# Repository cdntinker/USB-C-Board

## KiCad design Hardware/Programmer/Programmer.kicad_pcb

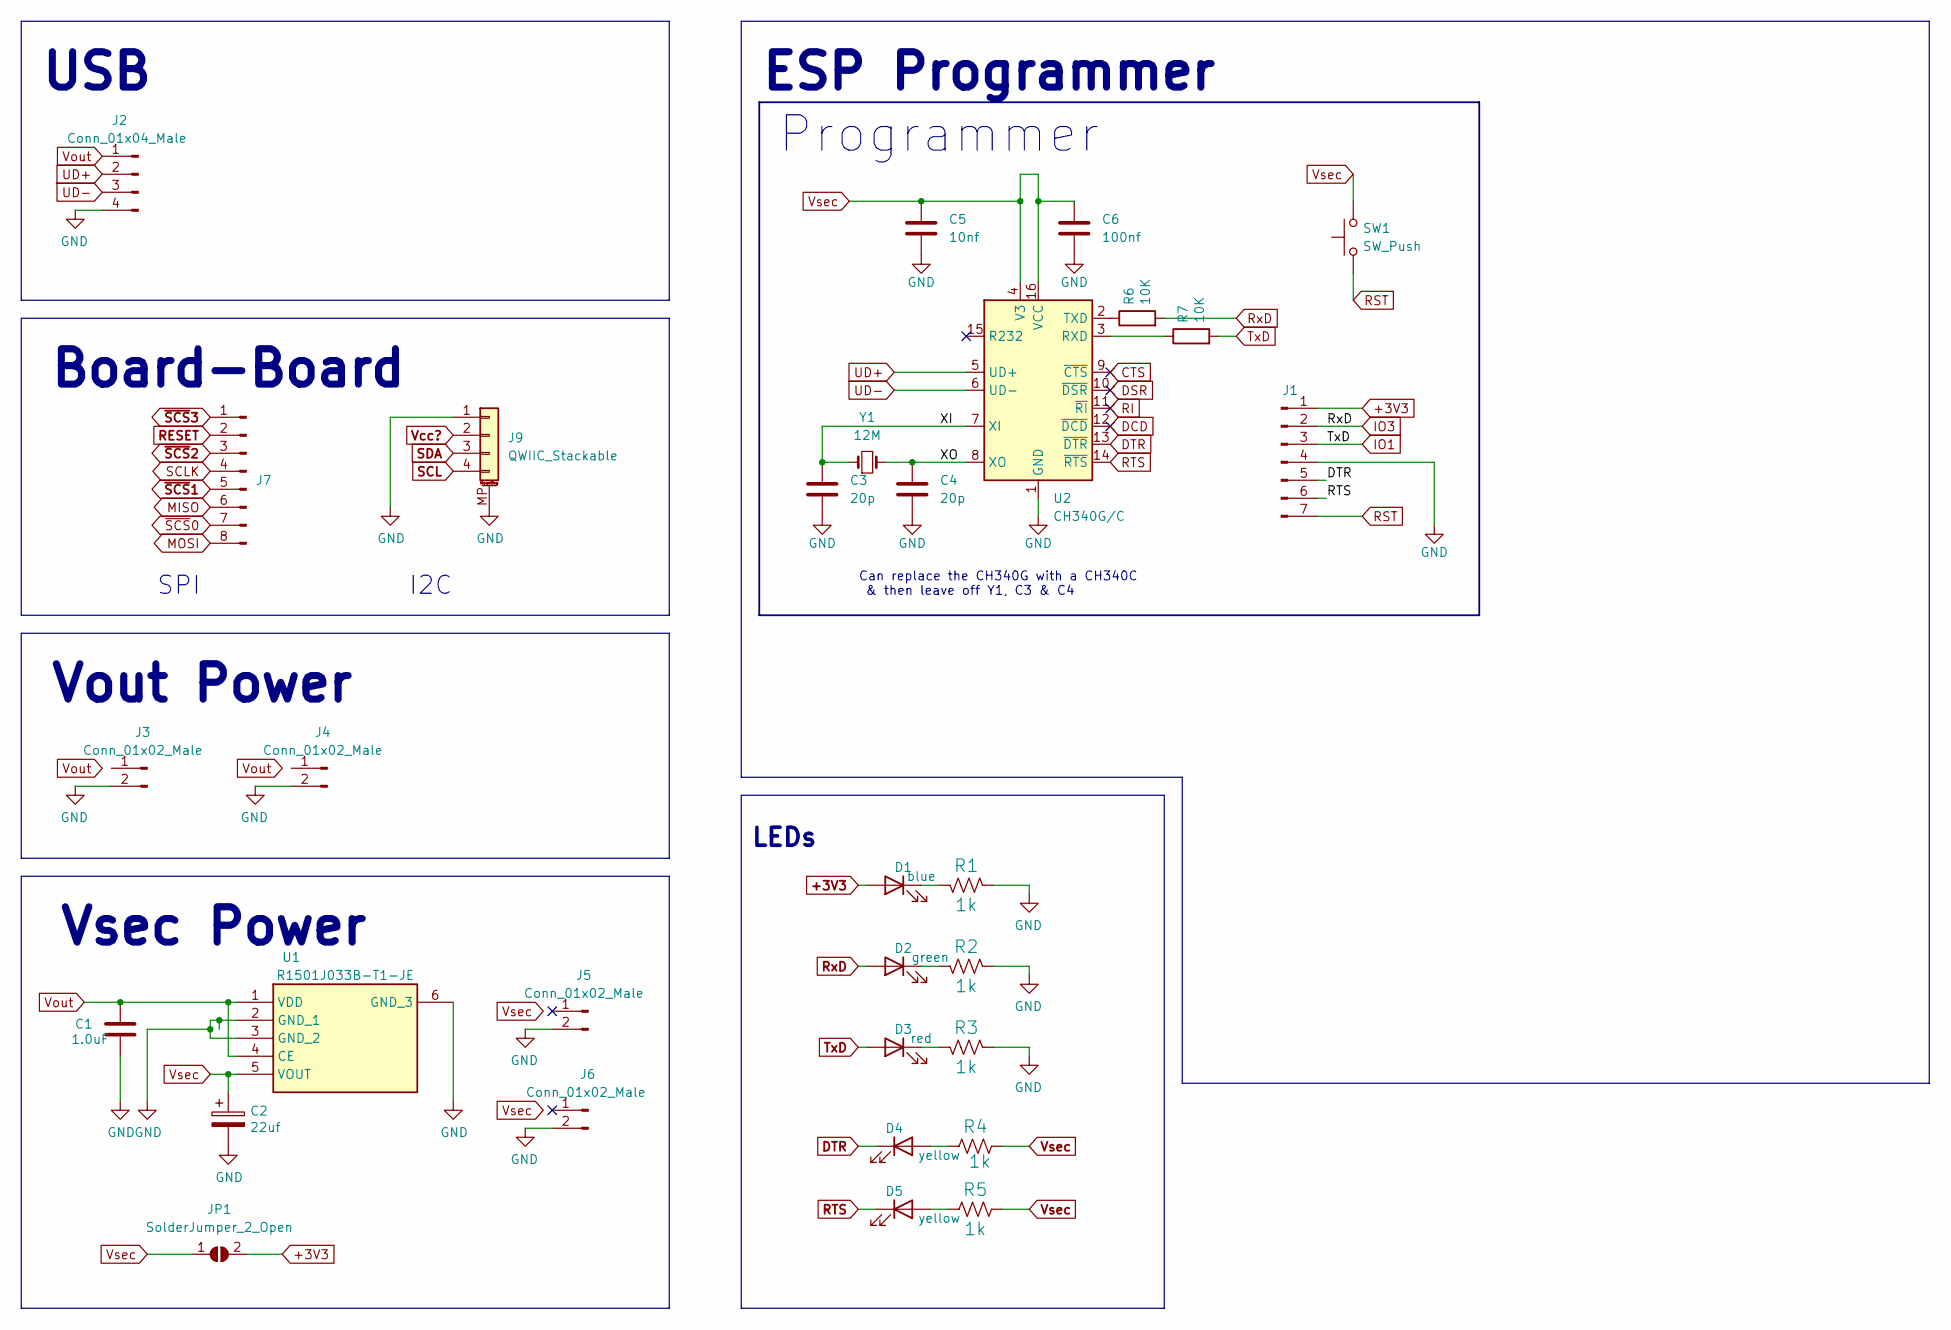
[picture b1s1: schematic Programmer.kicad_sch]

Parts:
C1: 1.0uF; C_0603_1608Metric; LCSC C559769
C2: 22uf; CP_EIA-6032-28-Tantalumm_HandSolder; LCSC C89246
C3, C4: 20p; C_0603_1608Metric_Pad1.08x0.95mm_HandSolder; LCSC C325469
C5: 10nf; C_0603_1608Metric_Pad1.08x0.95mm_HandSolder; LCSC C161232
C6: 100nf; C_0603_1608Metric_Pad1.08x0.95mm_HandSolder; LCSC C235731
D1: blue; LED_0603_1608Metric; LCSC C434420
D2: green; LED_0603_1608Metric; LCSC C434420
D3: red; LED_0603_1608Metric; LCSC C434420
D4: yellow; LED_0603_1608Metric; LCSC C434421
D5: yellow; LED_0603_1608Metric; LCSC C434424
J1: Conn_01x07_Male; Board_Stacker_7
J2: Conn_01x04_Male; Board_Stacker_4
J3, J4, J5, J6: Conn_01x02_Male; Board_Stacker_2
J7: Conn_01x08_Male; PinHeader_2x04_P1.27mm_Vertical; LCSC C2881786 + C2684732
J9: QWIIC_Stackable; QWIIC_Stack_II
JP1: SolderJumper_2_Open; SolderJumper-2_P_Open_Rounded_skinny
R1, R2, R3, R4, R5: 1k; R_0603_1608Metric; LCSC C21190
R6, R7: 10K; R_0603_1608Metric_Pad0.98x0.95mm_HandSolder; LCSC C25804
SW1: SW_Push; SW_Push_TS273014TP; LCSC C2858276
U1: R1501J033B-T1-JE; R1501J033BT1JE; Manufacturer_Part_Number R1501J033B-T1-JE; LCSC C3748149
U2: CH340G/C; SOIC-16_3.9x9.9mm_P1.27mm; LCSC C14267/C84681
Y1: 12M; Crystal_SMD_5032-2Pin_5.0x3.2mm; LCSC C2842275

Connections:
+3V3: D1.2 (A), J1.1, JP1.2 (B)
/XI: C3.1, U2.7 (XI), Y1.1
/XO: C4.1, U2.8 (XO), Y1.2
CTS: U2.9 (~CTS)
DCD: U2.12 (~DCD)
DSR: U2.10 (~DSR)
DTR: D4.1 (K), J1.5, U2.13 (~DTR)
GND: C1.2, C2.2, C3.2, C4.2, C5.2, C6.2, J1.4, J2.4, J3.2, J4.2, J5.2, J6.2, J9.1, J9.MP (MountPin), R1.1, R2.1, R3.1, U1.2 (GND_1), U1.3 (GND_2), U1.6 (GND_3), U2.1 (GND)
IO1: D3.2 (A), J1.3, R7.2
IO3: D2.2 (A), J1.2, R6.2
MISO: J7.6
MOSI: J7.8
unnamed: D1.1 (K), R1.2
unnamed: D2.1 (K), R2.2
unnamed: D3.1 (K), R3.2
unnamed: D4.2 (A), R4.1
unnamed: D5.2 (A), R5.1
unnamed: R6.1, U2.2 (TXD)
unnamed: R7.1, U2.3 (RXD)
RESET: J7.2
RI: U2.11 (~RI)
RST: J1.7, SW1.1
RTS: D5.1 (K), J1.6, U2.14 (~RTS)
SCL: J9.4
SCLK: J7.4
SDA: J9.3
UD+: J2.2, U2.5 (UD+)
UD-: J2.3, U2.6 (UD-)
Vcc?: J9.2
Vout: C1.1, J2.1, U1.1 (VDD), U1.4 (CE)
Vsec: C2.1, C5.1, C6.1, JP1.1 (A), R4.2, R5.2, SW1.2, U1.5 (VOUT), U2.4 (V3), U2.16 (VCC)
~RESET: J7.1
~SCS0: J7.7
~SCS1: J7.5
~SCS2: J7.3

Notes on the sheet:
Vout Power
USB
Programmer
LEDs
Can replace the CH340G with a CH340C & then leave off Y1, C3 & C4
I2C
Board-Board
ESP Programmer
Vsec Power
SPI

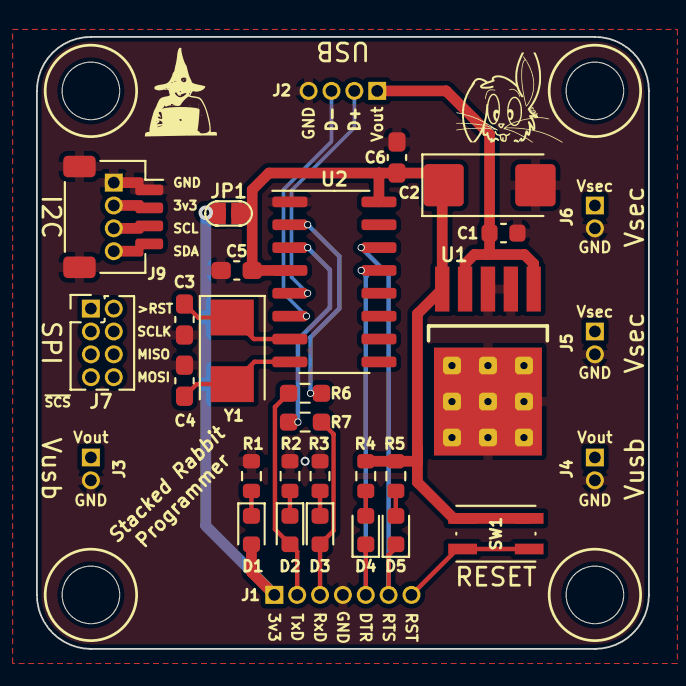
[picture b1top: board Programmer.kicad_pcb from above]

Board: 2 copper layers, 34.0 x 34.0 mm, 31 parts (0 on the bottom side), 20 nets.

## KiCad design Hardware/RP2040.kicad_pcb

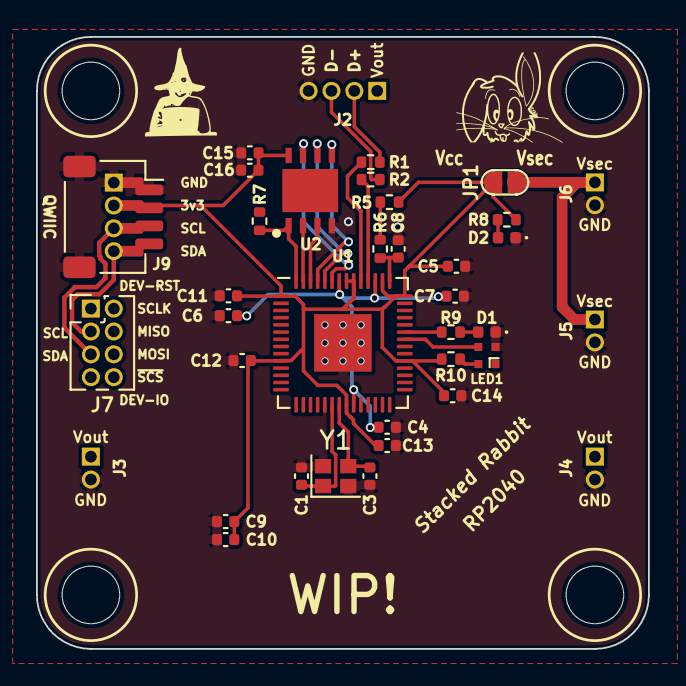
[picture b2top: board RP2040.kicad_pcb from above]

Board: 2 copper layers, 34.0 x 34.0 mm, 37 parts (0 on the bottom side), 25 nets.

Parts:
C1, C3: 20p; C_0402_1005Metric
C4, C5, C8, C15: 2u2; C_0402_1005Metric
C6, C7, C9, C10, C11, C12, C13, C14, C16: 100n; C_0402_1005Metric
D1, D2: LED; LED_0402_1005Metric
J2: Conn_01x04_Male; Board_Stacker_4
J3, J4, J5, J6: Conn_01x02_Male; Board_Stacker_2
J7: Conn_01x08_Male; PinHeader_2x04_P1.27mm_Vertical
J9: QWIIC_Stackable; QWIIC_Stack_II
JP1: SolderJumper_2_Open; SolderJumper-2_P_Open_Rounded_skinny
LED1: XL-1010RGBC-WS2812B; XL1010RGBCWS2812B
R1, R2: 27; R_0402_1005Metric
R5: 200; R_0402_1005Metric
R6: 1; R_0402_1005Metric
R7: 1k; R_0402_1005Metric
R8: 2k2; R_0402_1005Metric
R9: 470; R_0402_1005Metric
R10: ???; R_0402_1005Metric
U1: RP2040; QFN-56-1EP_7x7mm_P0.4mm_EP3.2x3.2mm
U2: W25Q32JVXGIQ; SON80P400X400X50-9N
Y1: 12MHz; Crystal_SMD_2016-4Pin_2.0x1.6mm

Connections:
+1V1: C4.2, C6.1, C7.1, U1.23 (DVDD), U1.45 (VREG_VOUT), U1.50 (DVDD)
+3V3: C5.1, C9.1, C10.1, C11.1, C12.1, C13.1, C14.1, C15.2, C16.1, J9.2, JP1.2 (B), R5.2, R8.1, R10.1, U1.1 (IOVDD), U1.10 (IOVDD), U1.22 (IOVDD), U1.33 (IOVDD), U1.42 (IOVDD), U1.44 (VREG_IN), U1.48 (USB_VDD), U1.49 (IOVDD), U2.8 (VCC)
/USB_DM: R2.2, U1.46 (USB_DM)
/USB_DP: R1.2, U1.47 (USB_DP)
/Xin: C1.1, U1.20 (XIN), Y1.1
/Xout: C3.1, U1.21 (XOUT), Y1.3
ADC_REF: R5.1, R6.2
GND: C1.2, C3.2, C4.1, C5.2, C6.2, C7.2, C8.1, C9.2, C10.2, C11.2, C12.2, C13.2, C14.2, C15.1, C16.2, D1.1 (K), D2.1 (K), J2.4, J3.2, J4.2, J5.2, J6.2, J9.1, J9.MP (MountPin), LED1.3 (GND), U1.19 (TESTEN), U1.57 (GND), U2.4 (GND), Y1.2, Y1.4
unnamed: D1.2 (A), R9.2
unnamed: D2.2 (A), R8.2
unnamed: LED1.2 (VDD), R10.2
unnamed: C8.2, R6.1, U1.43 (ADC_AVDD)
QSPI SS: R7.1, U1.56 (QSPI_SS), U2.1 (~CS)
QSPI_SCLK: U1.52 (QSPI_SCLK), U2.6 (CLK)
QSPI_SD0: U1.53 (QSPI_SD0), U2.5 (DI(IO0))
QSPI_SD1: U1.55 (QSPI_SD1), U2.2 (DO(IO1))
QSPI_SD2: U1.54 (QSPI_SD2), U2.3 (IO2)
QSPI_SD3: U1.51 (QSPI_SD3), U2.7 (IO3)
SCL: J7.3, J9.4
SDA: J7.5, J9.3
UD+: J2.2, R1.1
UD-: J2.3, R2.1
Vsec: J5.1, J6.1, JP1.1 (A)
io24: LED1.4 (DI), U1.36 (GPIO24)
io25: R9.1, U1.37 (GPIO25)

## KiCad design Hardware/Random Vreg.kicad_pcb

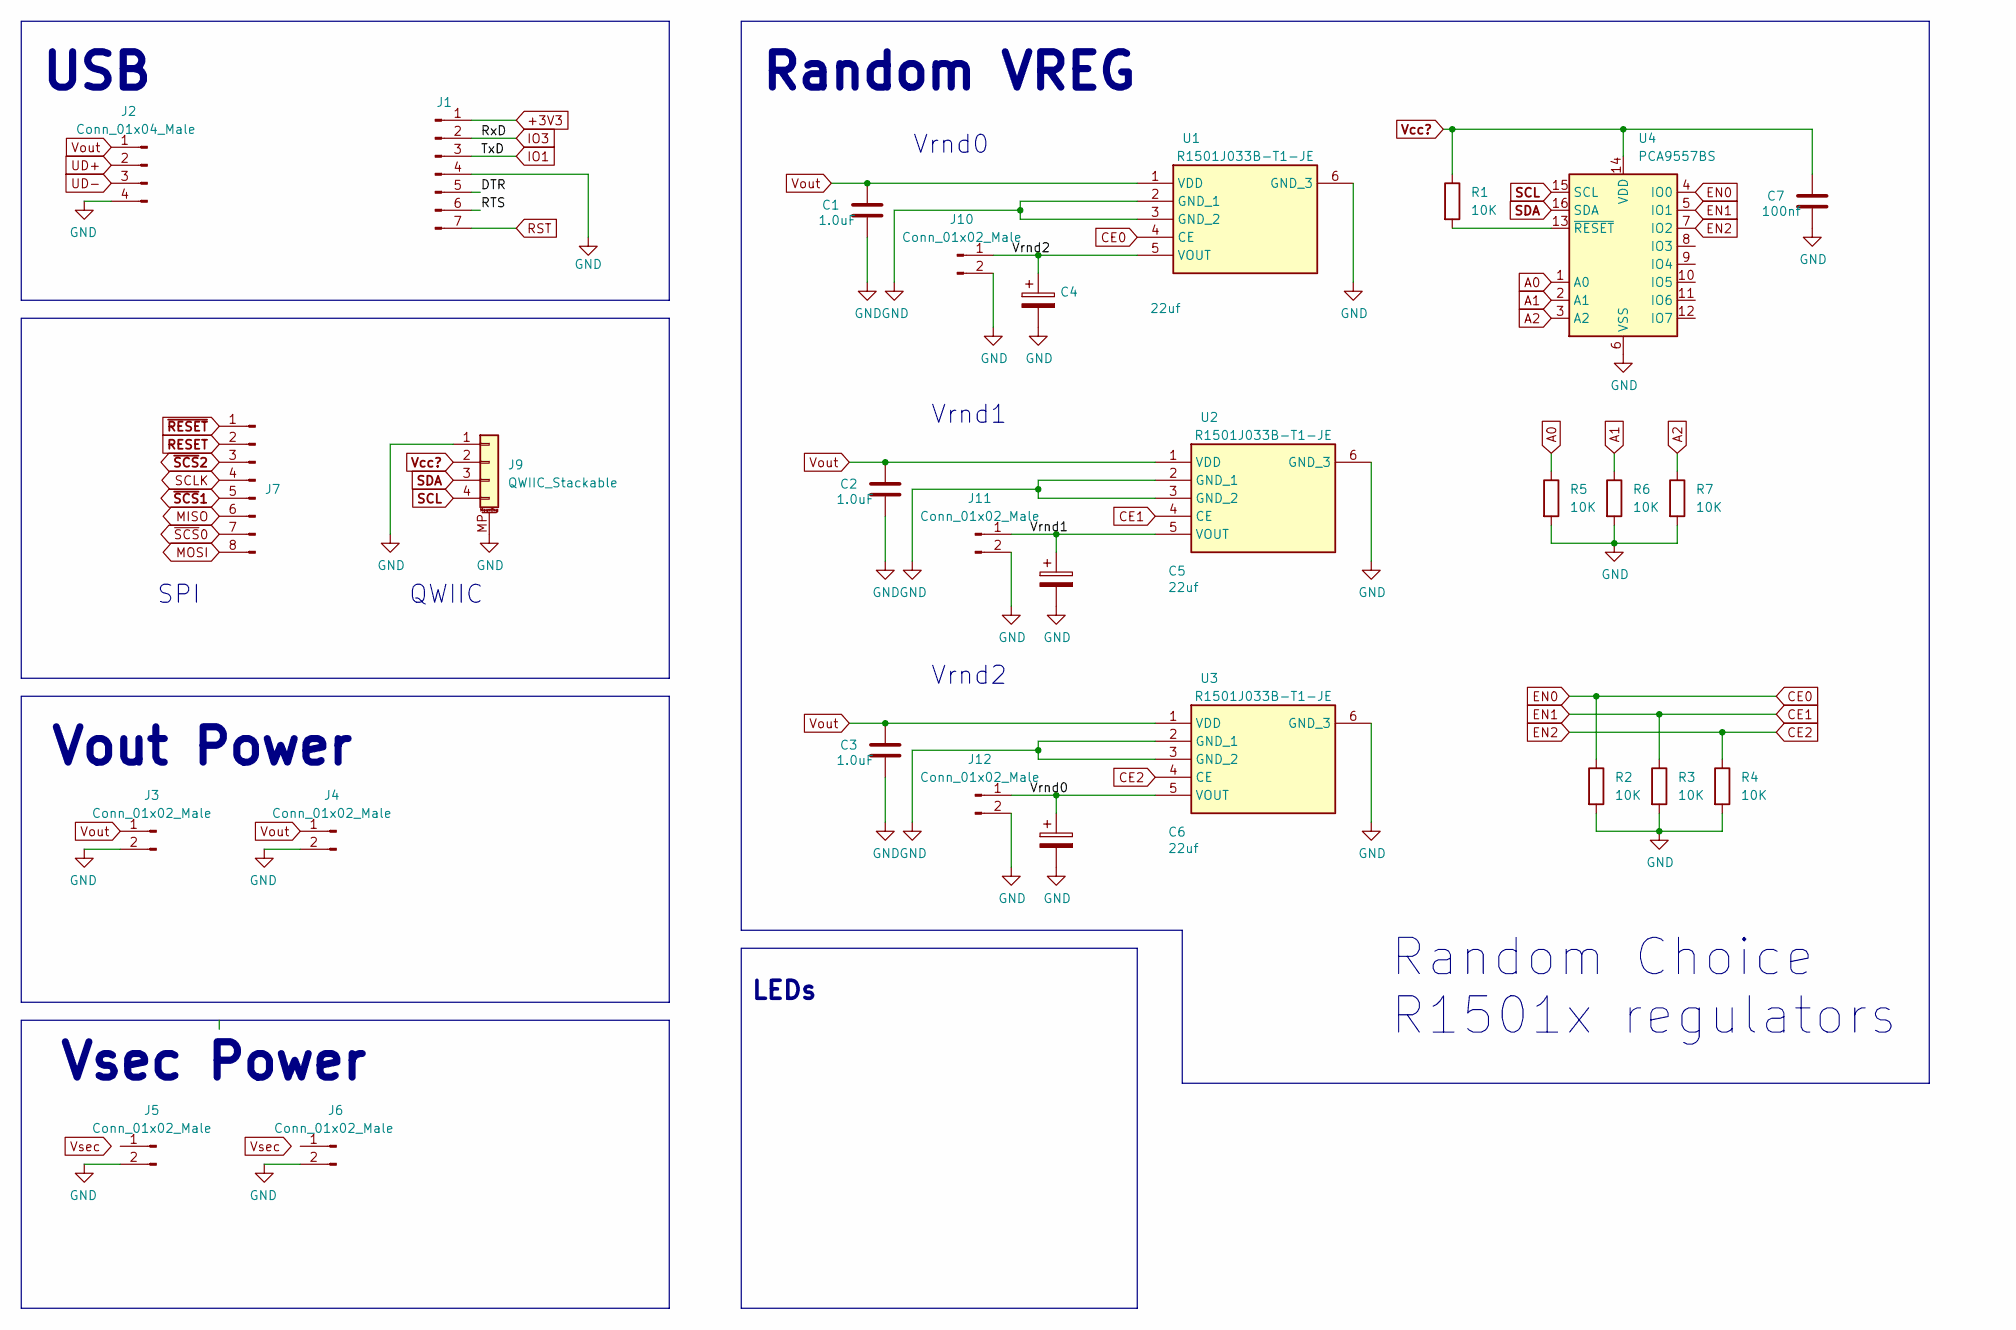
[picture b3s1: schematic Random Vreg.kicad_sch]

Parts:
C1, C2, C3: 1.0uF; C_0603_1608Metric; LCSC C559769
C4, C5, C6: 22uf; CP_EIA-6032-28-Tantalumm_HandSolder; LCSC C89246
C7: 100nf; C_0603_1608Metric; LCSC C559769
J1: Conn_01x07_Male; Board_Stacker_7
J2: Conn_01x04_Male; Board_Stacker_4
J3, J4, J5, J6, J10, J11, J12: Conn_01x02_Male; Board_Stacker_2
J7: Conn_01x08_Male; PinHeader_2x04_P1.27mm_Vertical; LCSC C2881786 + C2684732
J9: QWIIC_Stackable; QWIIC_Stack_II
R1, R2, R3, R4, R5, R6, R7: 10K; R_0603_1608Metric
U1, U2, U3: R1501J033B-T1-JE; R1501J033BT1JE; Manufacturer_Part_Number R1501J033B-T1-JE; LCSC C3748149
U4: PCA9557BS; HVQFN-16-1EP_3x3mm_P0.5mm_EP1.5x1.5mm

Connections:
/Vrnd0: C6.1, J12.1, U3.5 (VOUT)
/Vrnd1: C5.1, J11.1, U2.5 (VOUT)
/Vrnd2: C4.1, J10.1, U1.5 (VOUT)
A0: R5.1, U4.1 (A0)
A1: R6.1, U4.2 (A1)
A2: R7.1, U4.3 (A2)
CE0: R2.1, U1.4 (CE), U4.4 (IO0)
CE1: R3.1, U2.4 (CE), U4.5 (IO1)
CE2: R4.1, U3.4 (CE), U4.7 (IO2)
GND: C1.2, C2.2, C3.2, C4.2, C5.2, C6.2, C7.2, J1.4, J2.4, J3.2, J4.2, J5.2, J6.2, J9.1, J9.MP (MountPin), J10.2, J11.2, J12.2, R2.2, R3.2, R4.2, R5.2, R6.2, R7.2, U1.2 (GND_1), U1.3 (GND_2), U1.6 (GND_3), U2.2 (GND_1), U2.3 (GND_2), U2.6 (GND_3), U3.2 (GND_1), U3.3 (GND_2), U3.6 (GND_3), U4.6 (VSS)
MISO: J7.6
MOSI: J7.8
unnamed: R1.2, U4.13 (~RESET)
RESET: J7.2
SCL: J9.4, U4.15 (SCL)
SCLK: J7.4
SDA: J9.3, U4.16 (SDA)
UD+: J2.2
UD-: J2.3
Vcc?: C7.1, J9.2, R1.1, U4.14 (VDD)
Vout: C1.1, C2.1, C3.1, J2.1, J3.1, J4.1, U1.1 (VDD), U2.1 (VDD), U3.1 (VDD)
~RESET: J7.1
~SCS0: J7.7
~SCS1: J7.5
~SCS2: J7.3

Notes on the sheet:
Vsec Power
Vrnd1
Vout Power
QWIIC
Random Choice R1501x regulators
USB
Vrnd2
Random VREG
SPI
Vrnd0
LEDs

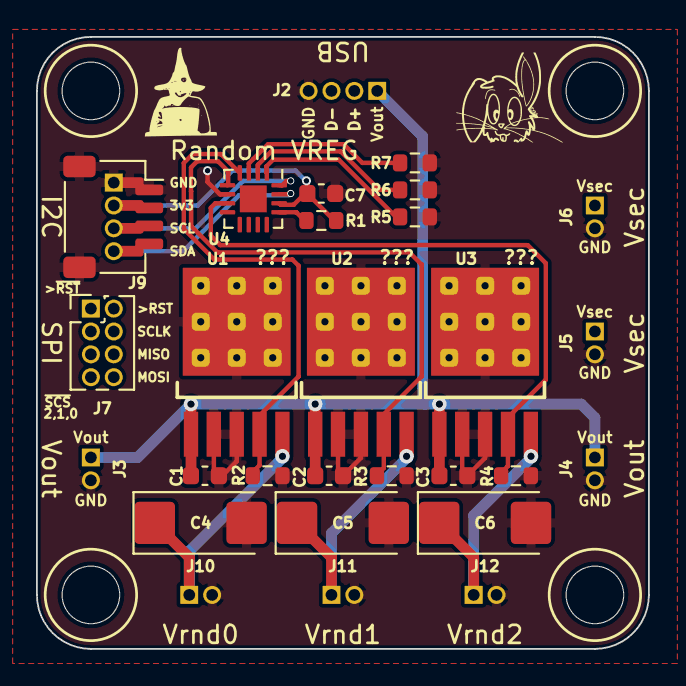
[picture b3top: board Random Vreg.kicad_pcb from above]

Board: 2 copper layers, 34.0 x 34.0 mm, 28 parts (0 on the bottom side), 15 nets.

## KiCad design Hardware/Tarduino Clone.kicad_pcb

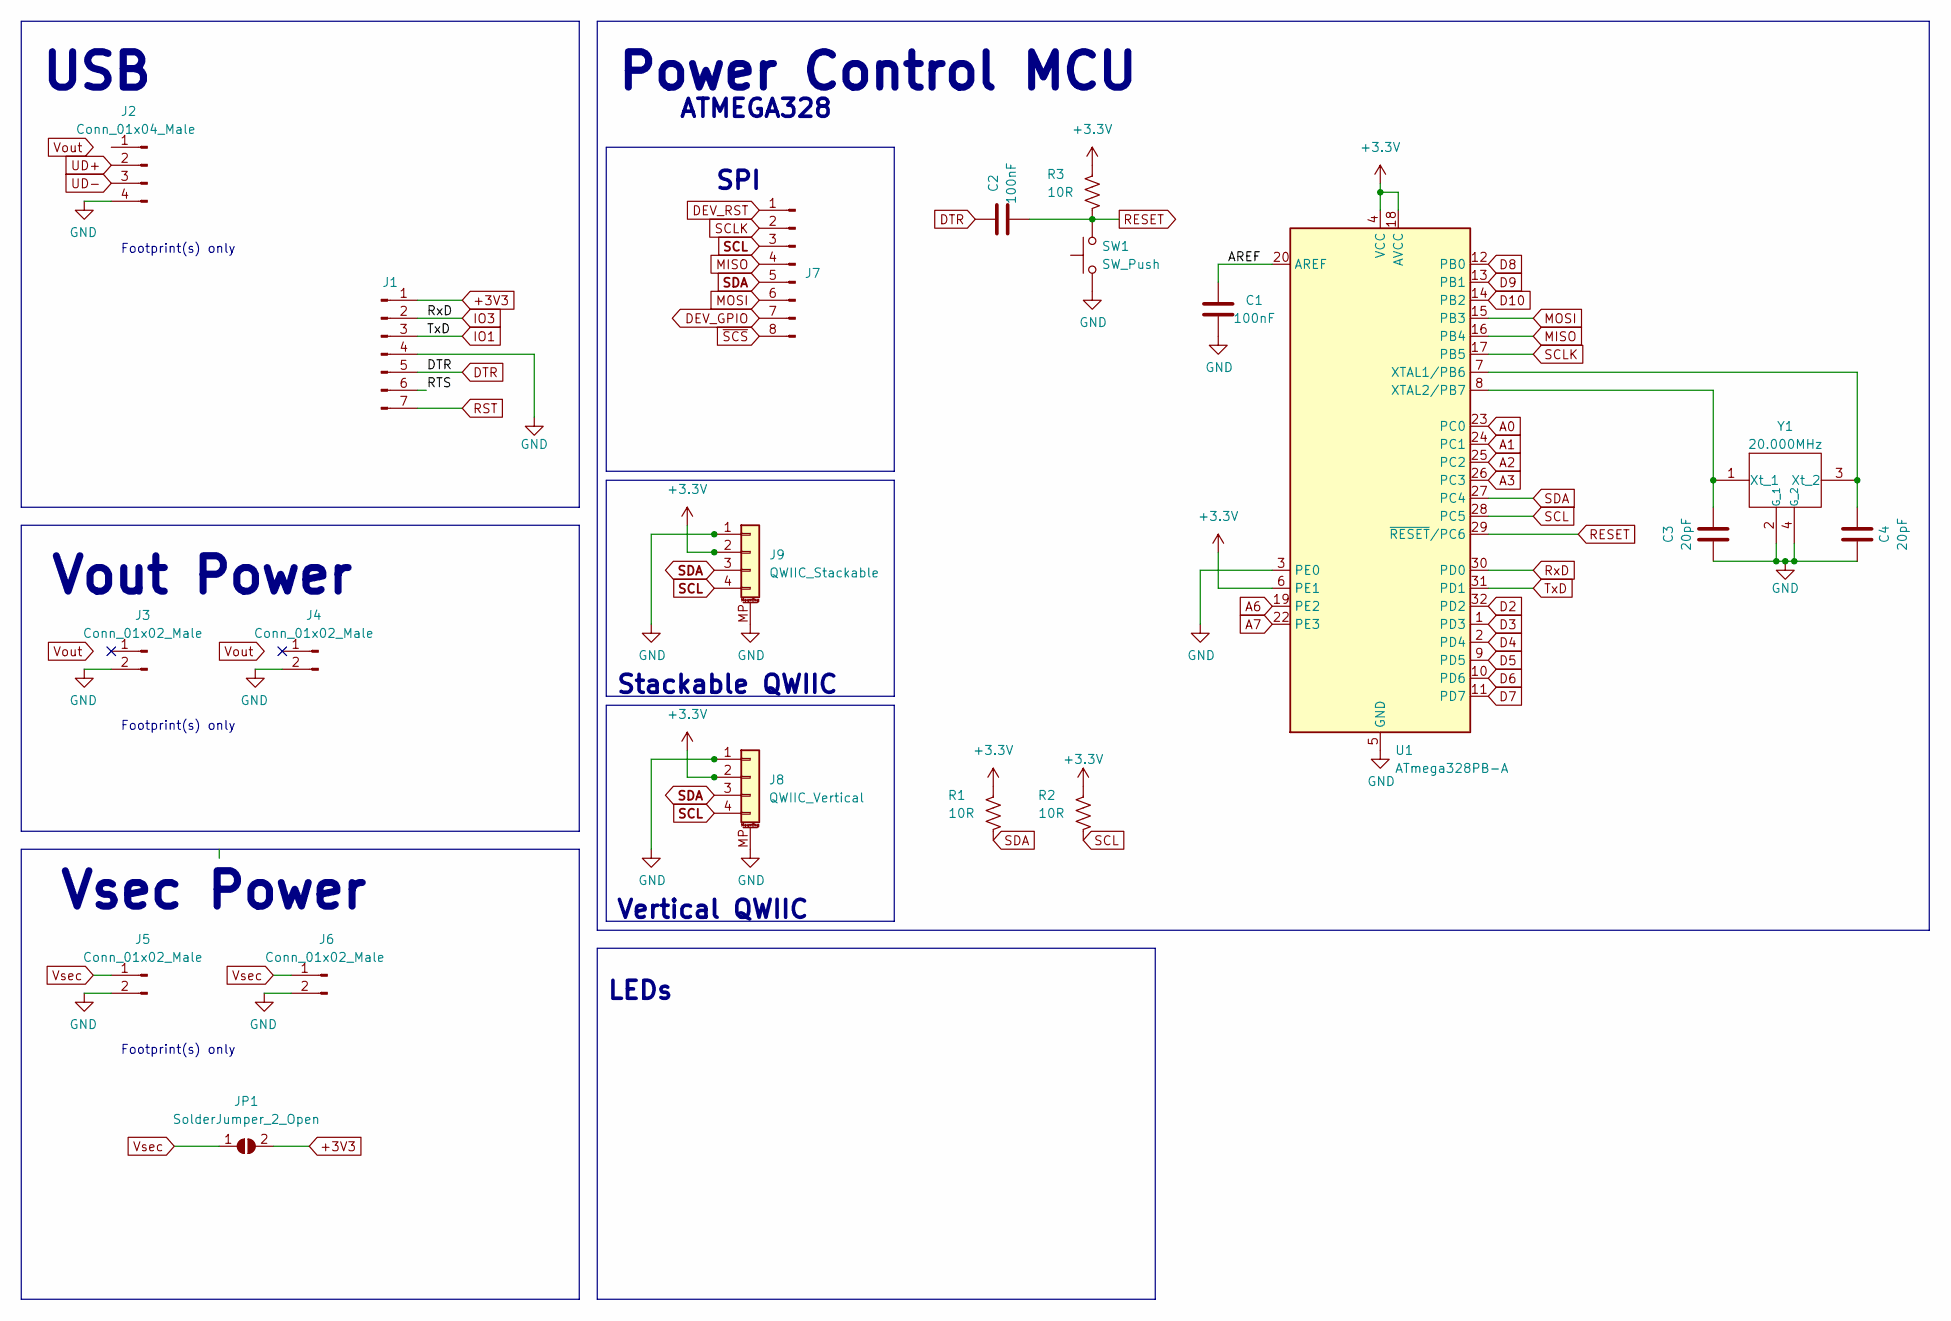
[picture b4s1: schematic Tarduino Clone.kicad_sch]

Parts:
C1, C2: 100nF; C_0603_1608Metric; LCSC C14663
C3, C4: 20pF; C_0603_1608Metric; LCSC C105621
J1: Conn_01x07_Male; Board_Stacker_7
J2: Conn_01x04_Male; Board_Stacker_4
J3, J4, J5, J6: Conn_01x02_Male; Board_Stacker_2
J7: Conn_01x08_Male; PinHeader_2x04_P1.27mm_Vertical; LCSC C2881786 + C2684732
J8: QWIIC_Vertical; LCSC C145961
J9: QWIIC_Stackable; QWIIC_Stack_II; LCSC C145956, C2881513, C2938401
JP1: SolderJumper_2_Open; SolderJumper-2_P_Open_Rounded_skinny
R1, R2, R3: 10R; R_0603_1608Metric; LCSC C103222
SW1: SW_Push; SW_Push_TS273014TP; LCSC C2858276
U1: ATmega328PB-A; TQFP-32_7x7mm_P0.8mm
Y1: 20.000MHz; ABM825000MHz10B1UT; LCSC C7294562

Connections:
/AREF: C1.2, U1.20 (AREF)
/RTS: J1.6
A0: U1.23 (PC0)
A1: U1.24 (PC1)
A2: U1.25 (PC2)
A3: U1.26 (PC3)
A6: U1.19 (PE2)
A7: U1.22 (PE3)
D2: U1.32 (PD2)
D3: U1.1 (PD3)
D4: U1.2 (PD4)
D5: U1.9 (PD5)
D6: U1.10 (PD6)
D7: U1.11 (PD7)
D8: U1.12 (PB0)
D9: U1.13 (PB1)
D10: U1.14 (PB2)
DEV_GPIO: J7.7
DEV_RST: J7.1
DTR: C2.2, J1.5
GND: C1.1, C3.1, C4.1, J1.4, J2.4, J3.2, J4.2, J5.2, J6.2, J8.1, J8.MP (MountPin), J9.1, J9.MP (MountPin), SW1.1, U1.3 (PE0), U1.5 (GND), U1.21 (GND), Y1.2 (G_1), Y1.4 (G_2)
IO1: J1.3, U1.31 (PD1)
IO3: J1.2, U1.30 (PD0)
MISO: J7.4, U1.16 (PB4)
MOSI: J7.6, U1.15 (PB3)
unnamed: C3.2, U1.8 (XTAL2/PB7), Y1.1 (Xt_1)
unnamed: C4.2, U1.7 (XTAL1/PB6), Y1.3 (Xt_2)
RESET: C2.1, R3.1, SW1.2, U1.29 (~RESET/PC6)
RST: J1.7
SCL: J7.3, J8.4, J9.4, R2.1, U1.28 (PC5)
SCLK: J7.2, U1.17 (PB5)
SDA: J7.5, J8.3, J9.3, R1.1, U1.27 (PC4)
UD+: J2.2
UD-: J2.3
Vsec: J5.1, J6.1, JP1.1 (A)
~SCS: J7.8

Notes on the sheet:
Vsec Power
Vout Power
Footprint(s) only
Vertical QWIIC
Stackable QWIIC
ATMEGA328
USB
SPI
Power Control MCU
LEDs

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
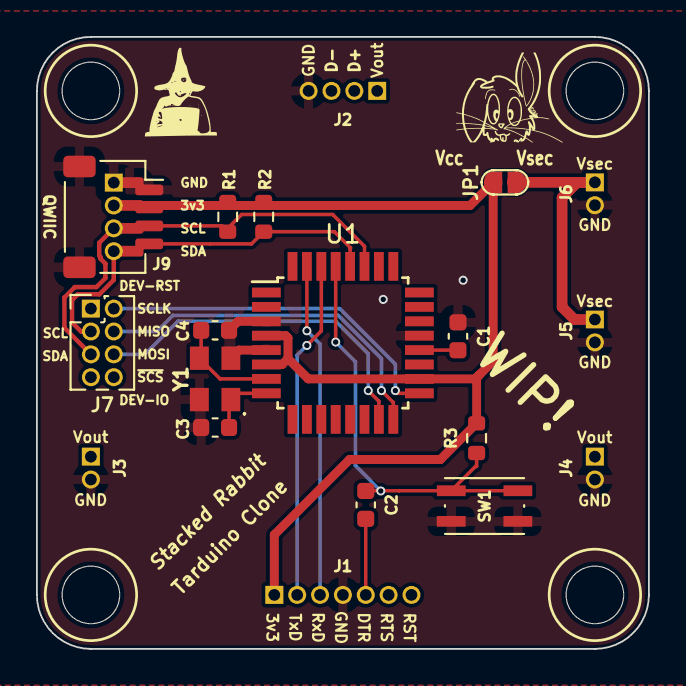
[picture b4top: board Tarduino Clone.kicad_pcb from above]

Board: 2 copper layers, 34.0 x 34.0 mm, 19 parts (0 on the bottom side), 15 nets.
